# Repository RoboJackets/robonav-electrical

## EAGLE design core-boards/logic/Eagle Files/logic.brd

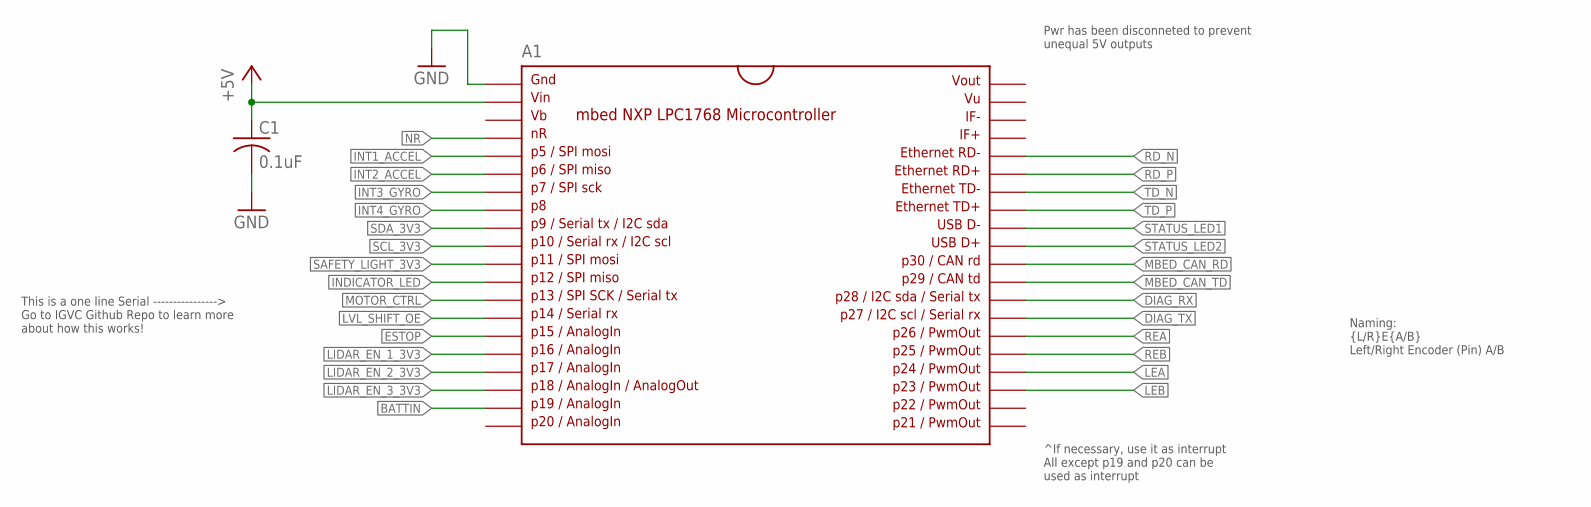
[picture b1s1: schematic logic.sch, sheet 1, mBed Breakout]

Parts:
A1: MBED1768; SPARKFUN-BOARDS_DIL40_0.9
C1: 0.1uF; C0603

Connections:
+5V: A1.2, C1.1; also elsewhere on the board
BATTIN: A1.19; also elsewhere on the board
DIAG_RX: A1.28; also elsewhere on the board
DIAG_TX: A1.27; also elsewhere on the board
ESTOP: A1.15; also elsewhere on the board
GND: A1.1, C1.2; also elsewhere on the board
INDICATOR_LED: A1.12; also elsewhere on the board
INT1_ACCEL: A1.5
INT2_ACCEL: A1.6
INT3_GYRO: A1.7
INT4_GYRO: A1.8
LEA: A1.24; also elsewhere on the board
LEB: A1.23; also elsewhere on the board
LIDAR_EN_1_3V3: A1.16; also elsewhere on the board
LIDAR_EN_2_3V3: A1.17; also elsewhere on the board
LIDAR_EN_3_3V3: A1.18; also elsewhere on the board
LVL_SHIFT_OE: A1.14; also elsewhere on the board
MBED_CAN_RD: A1.30; also elsewhere on the board
MBED_CAN_TD: A1.29; also elsewhere on the board
MOTOR_CTRL: A1.13; also elsewhere on the board
NR: A1.4; also elsewhere on the board
RD_N: A1.36; also elsewhere on the board
RD_P: A1.35; also elsewhere on the board
REA: A1.26; also elsewhere on the board
REB: A1.25; also elsewhere on the board
SAFETY_LIGHT_3V3: A1.11; also elsewhere on the board
SCL_3V3: A1.10; also elsewhere on the board
SDA_3V3: A1.9; also elsewhere on the board
STATUS_LED1: A1.32; also elsewhere on the board
STATUS_LED2: A1.31; also elsewhere on the board
TD_N: A1.34; also elsewhere on the board
TD_P: A1.33; also elsewhere on the board

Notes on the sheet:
Naming: {L/R}E{A/B} Left/Right Encoder (Pin) A/B
This is a one line Serial ----------------> Go to IGVC Github Repo to learn more about how this works!
^If necessary, use it as interrupt All except p19 and p20 can be used as interrupt
Pwr has been disconneted to prevent unequal 5V outputs

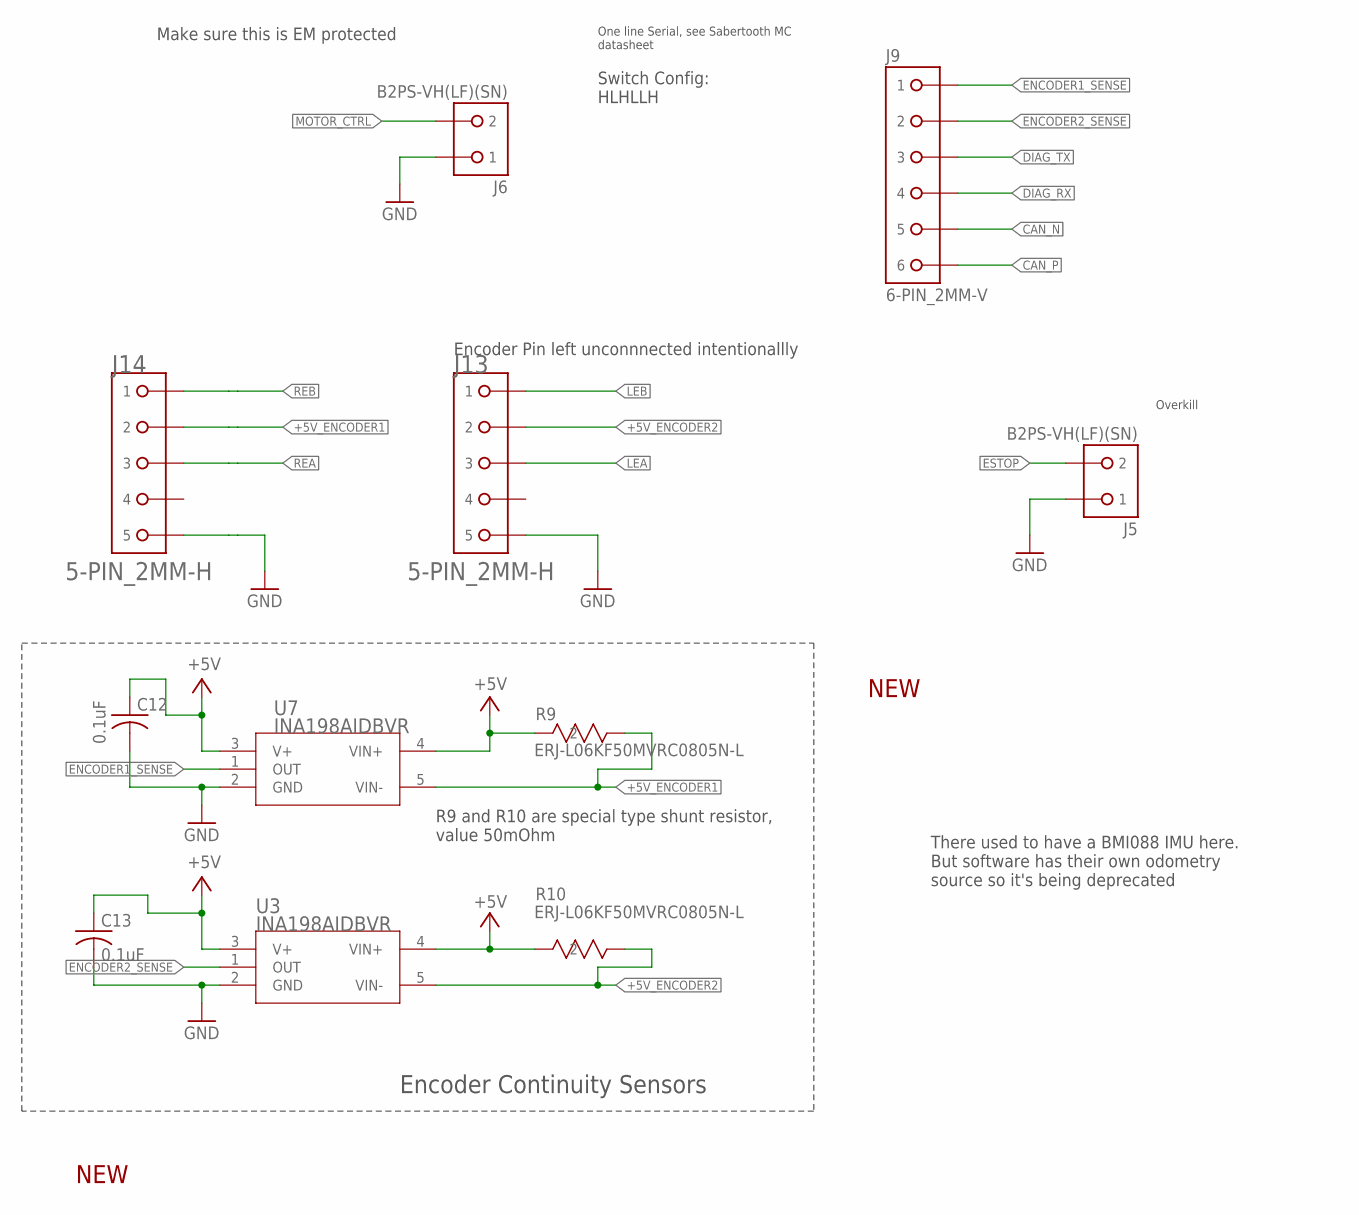
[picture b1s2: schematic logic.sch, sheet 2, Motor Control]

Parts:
C12, C13: 0.1uF; C0603
J5, J6: B2PS-VH(LF)(SN); B2PS-CENTERED
J9: 6-PIN_2MM-V; 2MM-6-V
J13, J14: 5-PIN_2MM-H; 2MM-5-H
R9, R10: ERJ-L06KF50MVRC0805N-L; RC0805N-L
U3, U7: INA198AIDBVR; DBV5

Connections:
+5V: C12.1, C13.1, R9.2, R10.2, U3.3 (V+), U3.4 (VIN+), U7.3 (V+), U7.4 (VIN+); also elsewhere on the board
+5V_ENCODER1: J14.2, R9.1, U7.5 (VIN-)
+5V_ENCODER2: J13.2, R10.1, U3.5 (VIN-)
CAN_N: J9.5; also elsewhere on the board
CAN_P: J9.6; also elsewhere on the board
DIAG_RX: J9.4; also elsewhere on the board
DIAG_TX: J9.3; also elsewhere on the board
ENCODER1_SENSE: J9.1, U7.1 (OUT)
ENCODER2_SENSE: J9.2, U3.1 (OUT)
ESTOP: J5.2; also elsewhere on the board
GND: C12.2, C13.2, J5.1, J6.1, J13.5, J14.5, U3.2 (GND), U7.2 (GND); also elsewhere on the board
LEA: J13.3; also elsewhere on the board
LEB: J13.1; also elsewhere on the board
MOTOR_CTRL: J6.2; also elsewhere on the board
REA: J14.3; also elsewhere on the board
REB: J14.1; also elsewhere on the board

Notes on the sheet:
Encoder Continuity Sensors
One line Serial, see Sabertooth MC datasheet
Encoder Pin left unconnnected intentionallly
Overkill
Make sure this is EM protected
There used to have a BMI088 IMU here. But software has their own odometry source so it's being deprecated
NEW
Switch Config: HLHLLH
R9 and R10 are special type shunt resistor, value 50mOhm

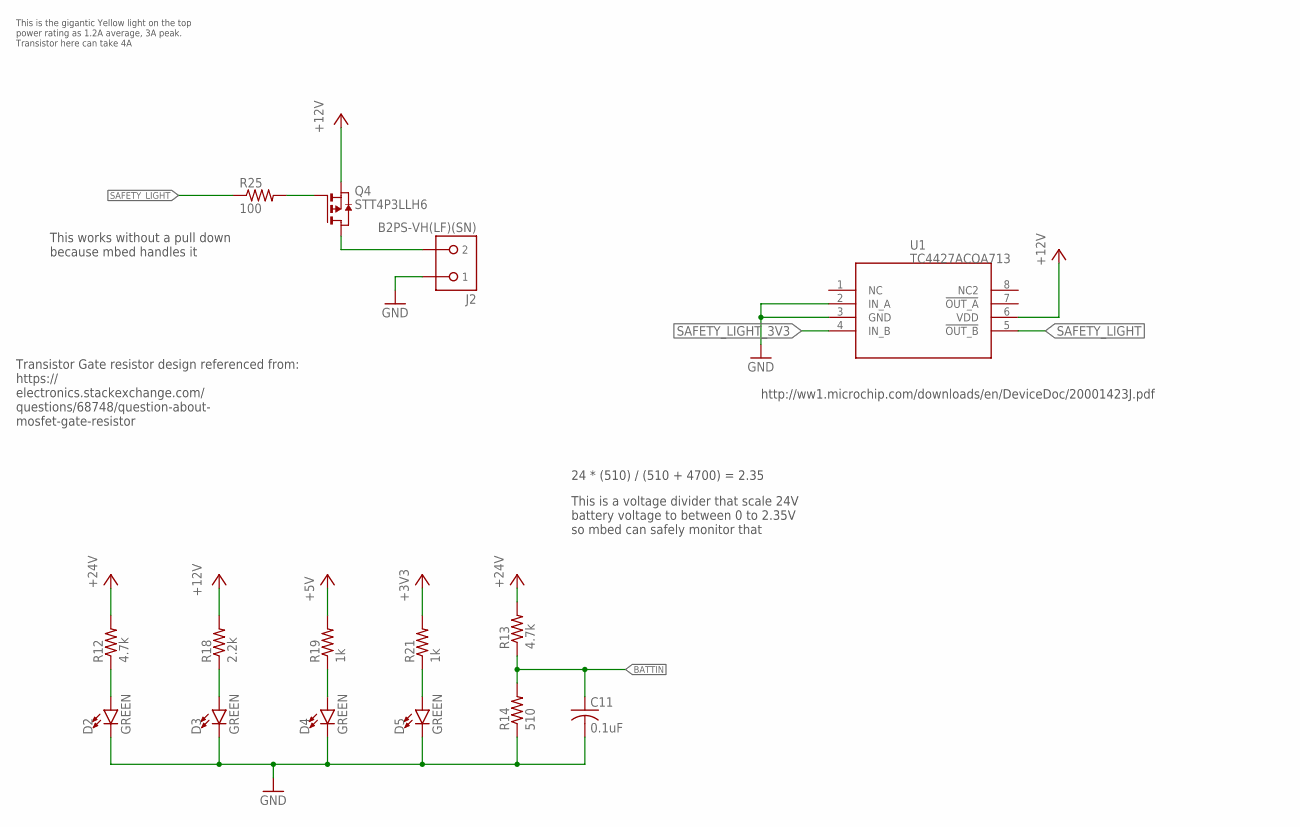
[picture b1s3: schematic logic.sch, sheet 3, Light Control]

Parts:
C11: 0.1uF; C0603
D2, D3, D4, D5: GREEN; LED-0603
J2: B2PS-VH(LF)(SN); B2PS-CENTERED
Q4: STT4P3LLH6; SOT23-6
R12, R13: 4.7k; R0603
R14: 510; R0603
R18: 2.2k; R0603
R19, R21: 1k; R0603
R25: 100; R0603
U1: TC4427ACOA713; SOIC-8

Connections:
3V3_LED_R: D5.A, R21.1
5V_LED_R: D4.A, R19.1
12V_LED_R: D3.A, R18.1
+3V3: R21.2; also elsewhere on the board
+5V: R19.2; also elsewhere on the board
+12V: Q4.4 (S), R18.2, U1.6 (VDD); also elsewhere on the board
+24V: R12.2, R13.2; also elsewhere on the board
BATTIN: C11.1, R13.1, R14.2; also elsewhere on the board
GND: C11.2, D2.C, D3.C, D4.C, D5.C, J2.1, R14.1, U1.2 (IN_A), U1.3 (GND); also elsewhere on the board
unnamed: D2.A, R12.1
SAFETY_HRD: J2.2, Q4.1 (D), Q4.2 (D), Q4.5 (D), Q4.6 (D)
SAFETY_LIGHT: R25.1, U1.5 (!OUT_B)
SAFETY_LIGHT_3V3: U1.4 (IN_B); also elsewhere on the board
SAFETY_R: Q4.3 (G), R25.2

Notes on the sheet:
This is the gigantic Yellow light on the top power rating as 1.2A average, 3A peak. Transistor here can take 4A
24 * (510) / (510 + 4700) = 2.35
Transistor Gate resistor design referenced from: https:// electronics.stackexchange.com/ questions/68748/question-about- mosfet-gate-resistor
http://ww1.microchip.com/downloads/en/DeviceDoc/20001423J.pdf
This is a voltage divider that scale 24V battery voltage to between 0 to 2.35V so mbed can safely monitor that
This works without a pull down because mbed handles it

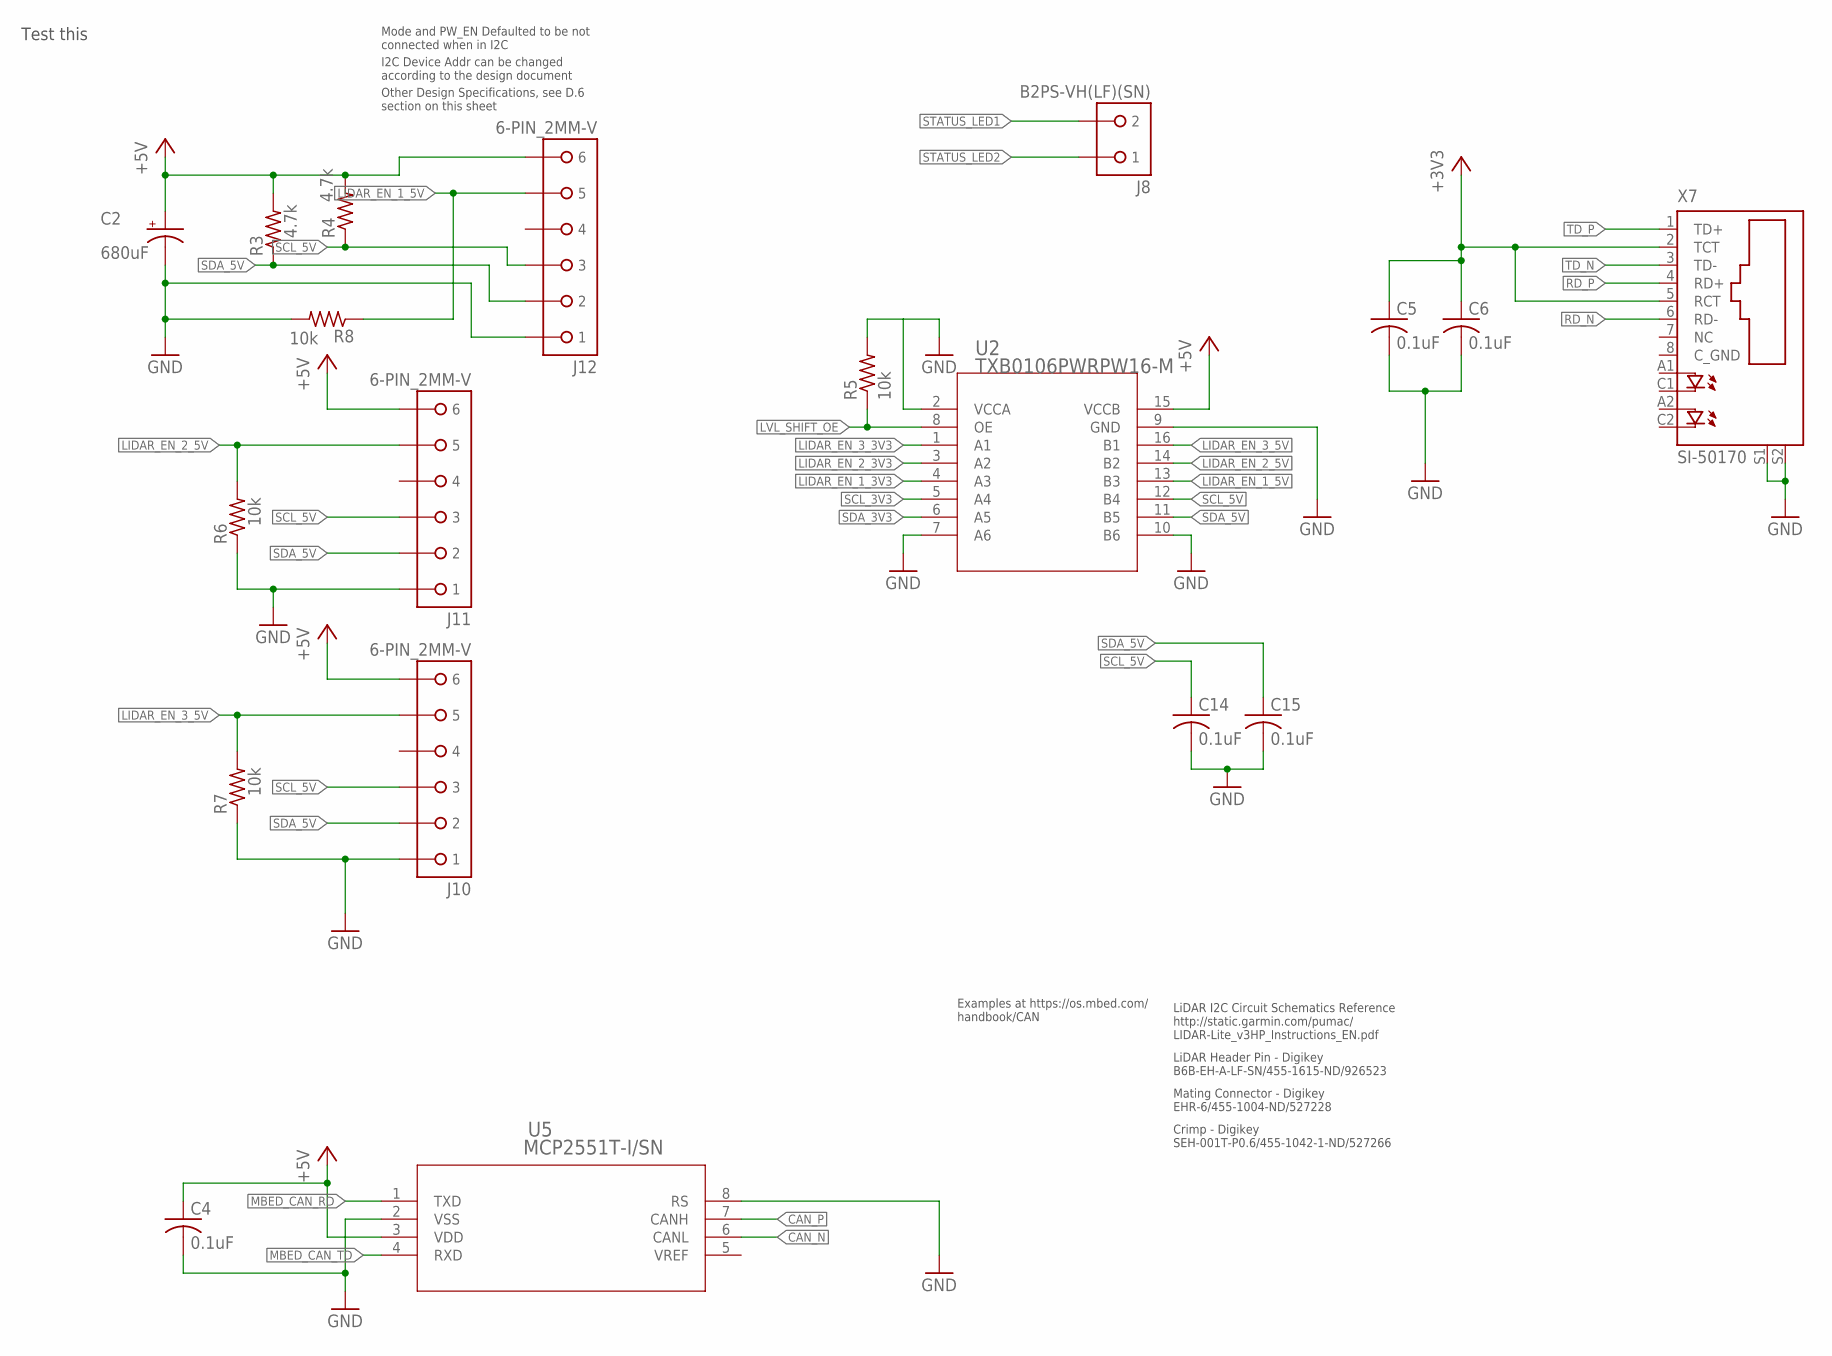
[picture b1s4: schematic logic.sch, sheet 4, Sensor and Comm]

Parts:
C2: 680uF; E5-5
C4, C5, C6, C14, C15: 0.1uF; C0603
J8: B2PS-VH(LF)(SN); B2PS-CENTERED
J10, J11, J12: 6-PIN_2MM-V; 2MM-6-V
R3, R4: 4.7k; R0603
R5, R6, R7, R8: 10k; R0603
U2: TXB0106PWRPW16-M; PW16-M
U5: MCP2551T-I/SN; SOIC8-N_MC
X7: SI-50170

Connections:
+3V3: C5.1, C6.1, X7.2 (TCT), X7.5 (RCT); also elsewhere on the board
+5V: C2.+, C4.1, J10.6, J11.6, J12.6, R3.2, R4.2, U2.15 (VCCB), U5.3 (VDD); also elsewhere on the board
CAN_N: U5.6 (CANL); also elsewhere on the board
CAN_P: U5.7 (CANH); also elsewhere on the board
GND: C2.-, C4.2, C5.2, C6.2, C14.2, C15.2, J10.1, J11.1, J12.1, R5.2, R6.1, R7.1, R8.2, U2.2 (VCCA), U2.7 (A6), U2.9 (GND), U2.10 (B6), U5.2 (VSS), U5.8 (RS), X7.S1, X7.S2; also elsewhere on the board
LIDAR_EN_1_3V3: U2.4 (A3); also elsewhere on the board
LIDAR_EN_1_5V: J12.5, R8.1, U2.13 (B3)
LIDAR_EN_2_3V3: U2.3 (A2); also elsewhere on the board
LIDAR_EN_2_5V: J11.5, R6.2, U2.14 (B2)
LIDAR_EN_3_3V3: U2.1 (A1); also elsewhere on the board
LIDAR_EN_3_5V: J10.5, R7.2, U2.16 (B1)
LVL_SHIFT_OE: R5.1, U2.8 (OE); also elsewhere on the board
MBED_CAN_RD: U5.1 (TXD); also elsewhere on the board
MBED_CAN_TD: U5.4 (RXD); also elsewhere on the board
RD_N: X7.6 (RD-); also elsewhere on the board
RD_P: X7.4 (RD+); also elsewhere on the board
SCL_3V3: U2.5 (A4); also elsewhere on the board
SCL_5V: C14.1, J10.3, J11.3, J12.3, R4.1, U2.12 (B4)
SDA_3V3: U2.6 (A5); also elsewhere on the board
SDA_5V: C15.1, J10.2, J11.2, J12.2, R3.1, U2.11 (B5)
STATUS_LED1: J8.2; also elsewhere on the board
STATUS_LED2: J8.1; also elsewhere on the board
TD_N: X7.3 (TD-); also elsewhere on the board
TD_P: X7.1 (TD+); also elsewhere on the board

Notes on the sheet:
LiDAR I2C Circuit Schematics Reference http://static.garmin.com/pumac/ LIDAR-Lite_v3HP_Instructions_EN.pdf
I2C Device Addr can be changed according to the design document
LiDAR Header Pin - Digikey B6B-EH-A-LF-SN/455-1615-ND/926523
Mating Connector - Digikey EHR-6/455-1004-ND/527228
Crimp - Digikey SEH-001T-P0.6/455-1042-1-ND/527266
Mode and PW_EN Defaulted to be not connected when in I2C
Examples at https://os.mbed.com/ handbook/CAN
Other Design Specifications, see D.6 section on this sheet
Test this

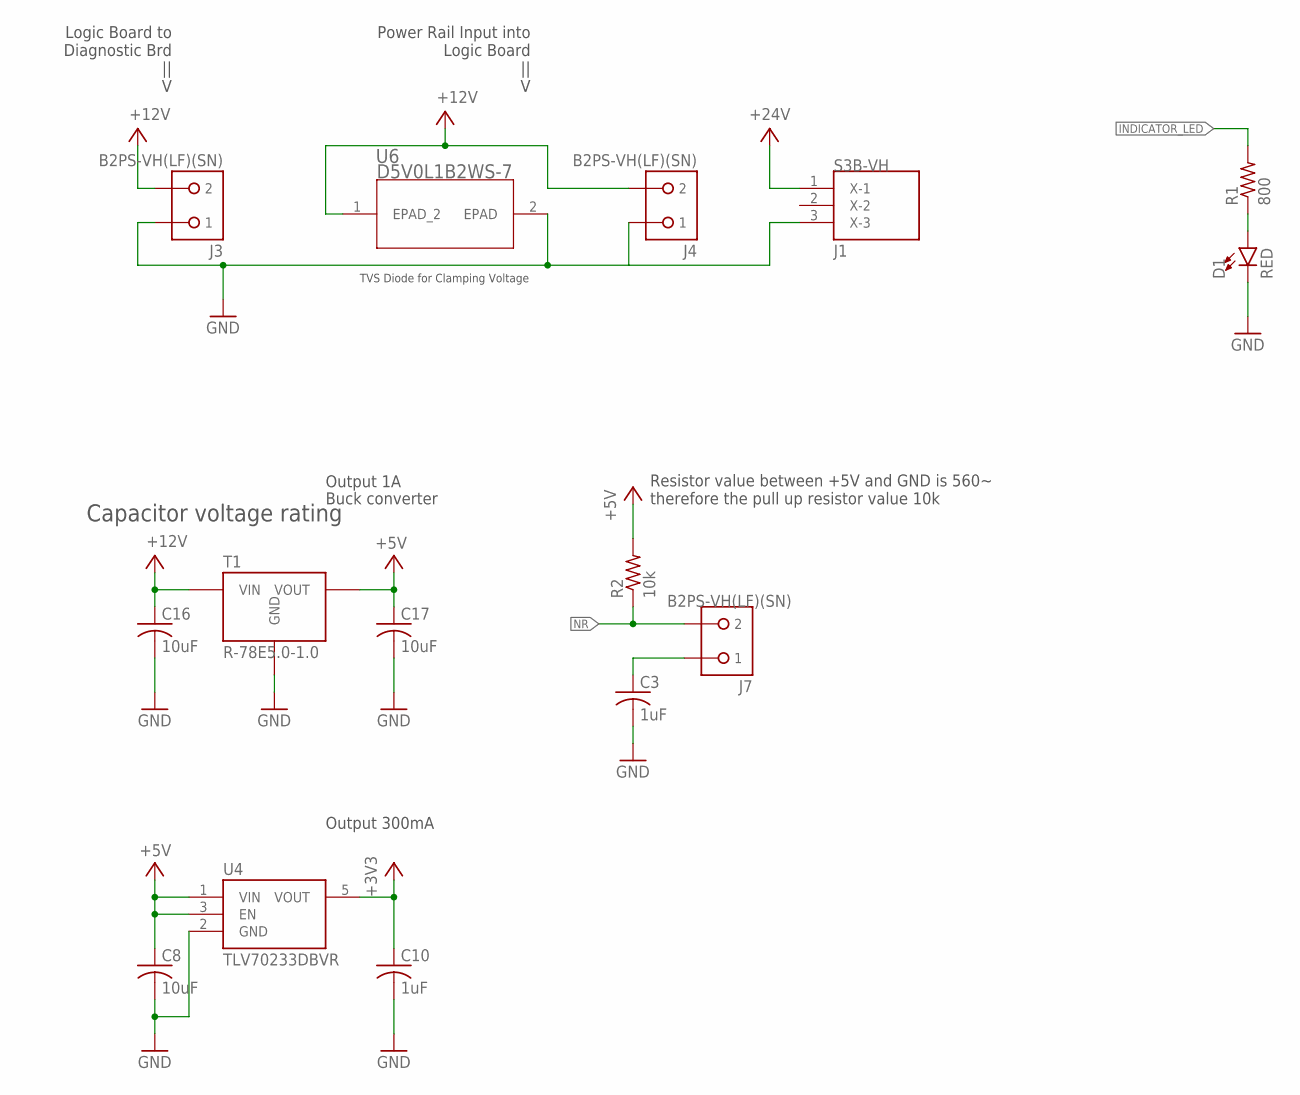
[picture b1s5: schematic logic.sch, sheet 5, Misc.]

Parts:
C3, C10: 1uF; C0805
C8, C16, C17: 10uF; C0805
D1: RED; LED-0603
J1: S3B-VH
J3, J4, J7: B2PS-VH(LF)(SN); B2PS-CENTERED
R1: 800; R0603
R2: 10k; R0603
T1: R-78E5.0-1.0; R-78E
U4: TLV70233DBVR; SOT-23-5
U6: D5V0L1B2WS-7; SOD323

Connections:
+3V3: C10.1, U4.5 (VOUT); also elsewhere on the board
+5V: C8.1, C17.1, R2.2, T1.3 (VOUT), U4.1 (VIN), U4.3 (EN); also elsewhere on the board
+12V: C16.1, J3.2, J4.2, T1.1 (VIN), U6.1 (EPAD_2); also elsewhere on the board
+24V: J1.1 (X-1); also elsewhere on the board
GND: C3.2, C8.2, C10.2, C16.2, C17.2, D1.C, J1.3 (X-3), J3.1, J4.1, T1.2 (GND), U4.2 (GND), U6.2 (EPAD); also elsewhere on the board
INDICATOR_LED: R1.2; also elsewhere on the board
unnamed: D1.A, R1.1
unnamed: C3.1, J7.1
NR: J7.2, R2.1; also elsewhere on the board

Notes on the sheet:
Buck converter
Output 1A
Output 300mA
Power Rail Input into Logic Board || V
Logic Board to Diagnostic Brd || V
Capacitor voltage rating
Resistor value between +5V and GND is 560~ therefore the pull up resistor value 10k
TVS Diode for Clamping Voltage

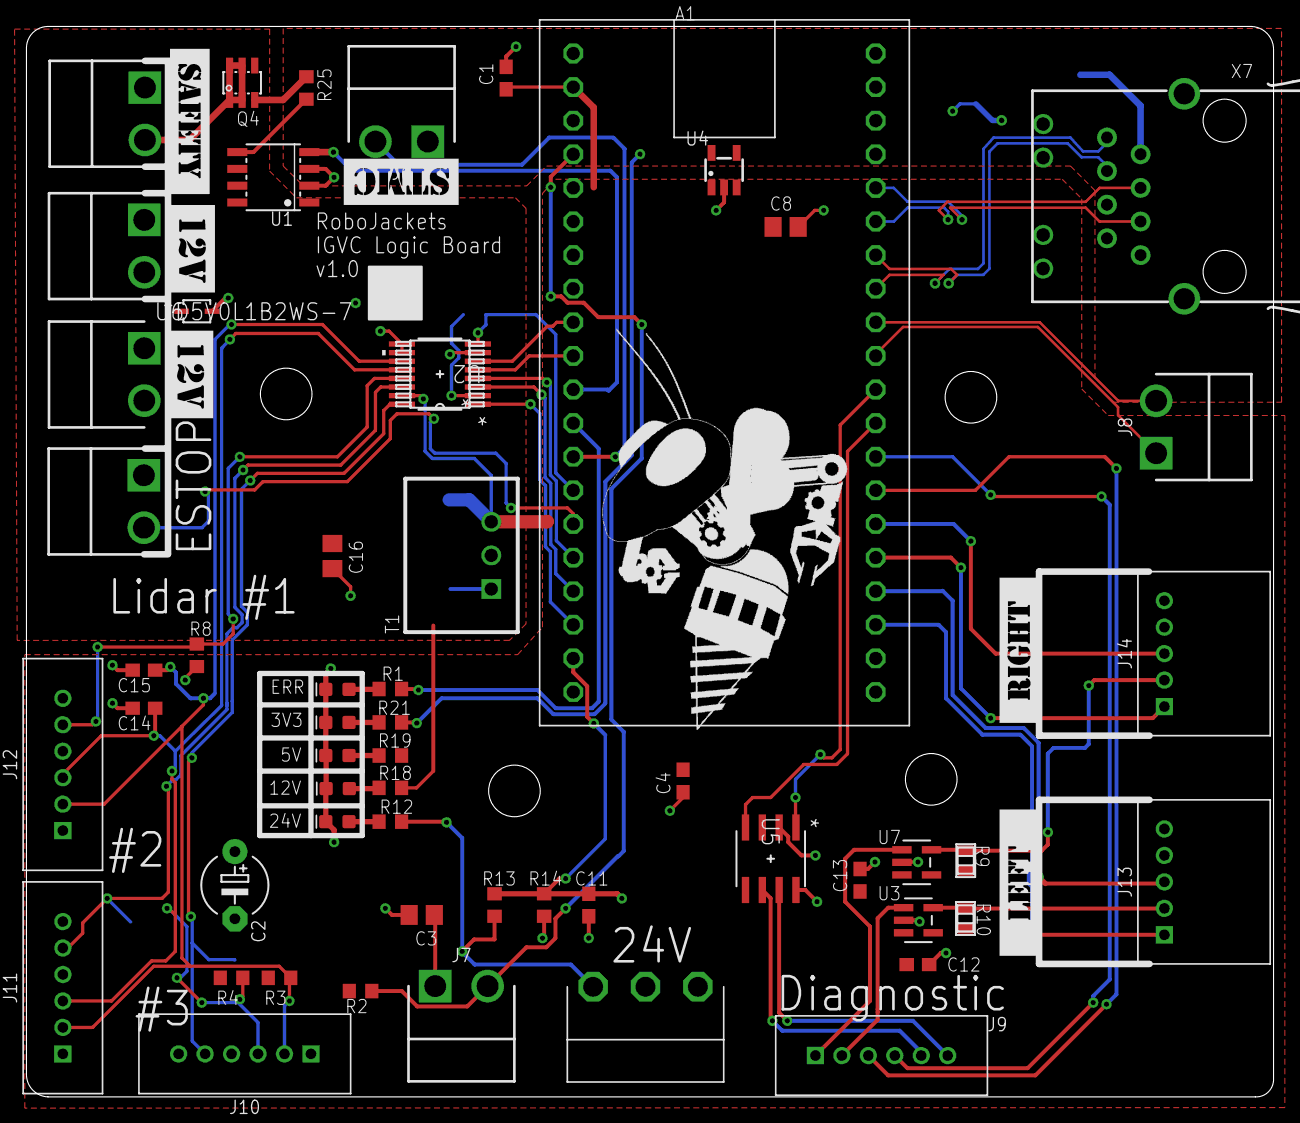
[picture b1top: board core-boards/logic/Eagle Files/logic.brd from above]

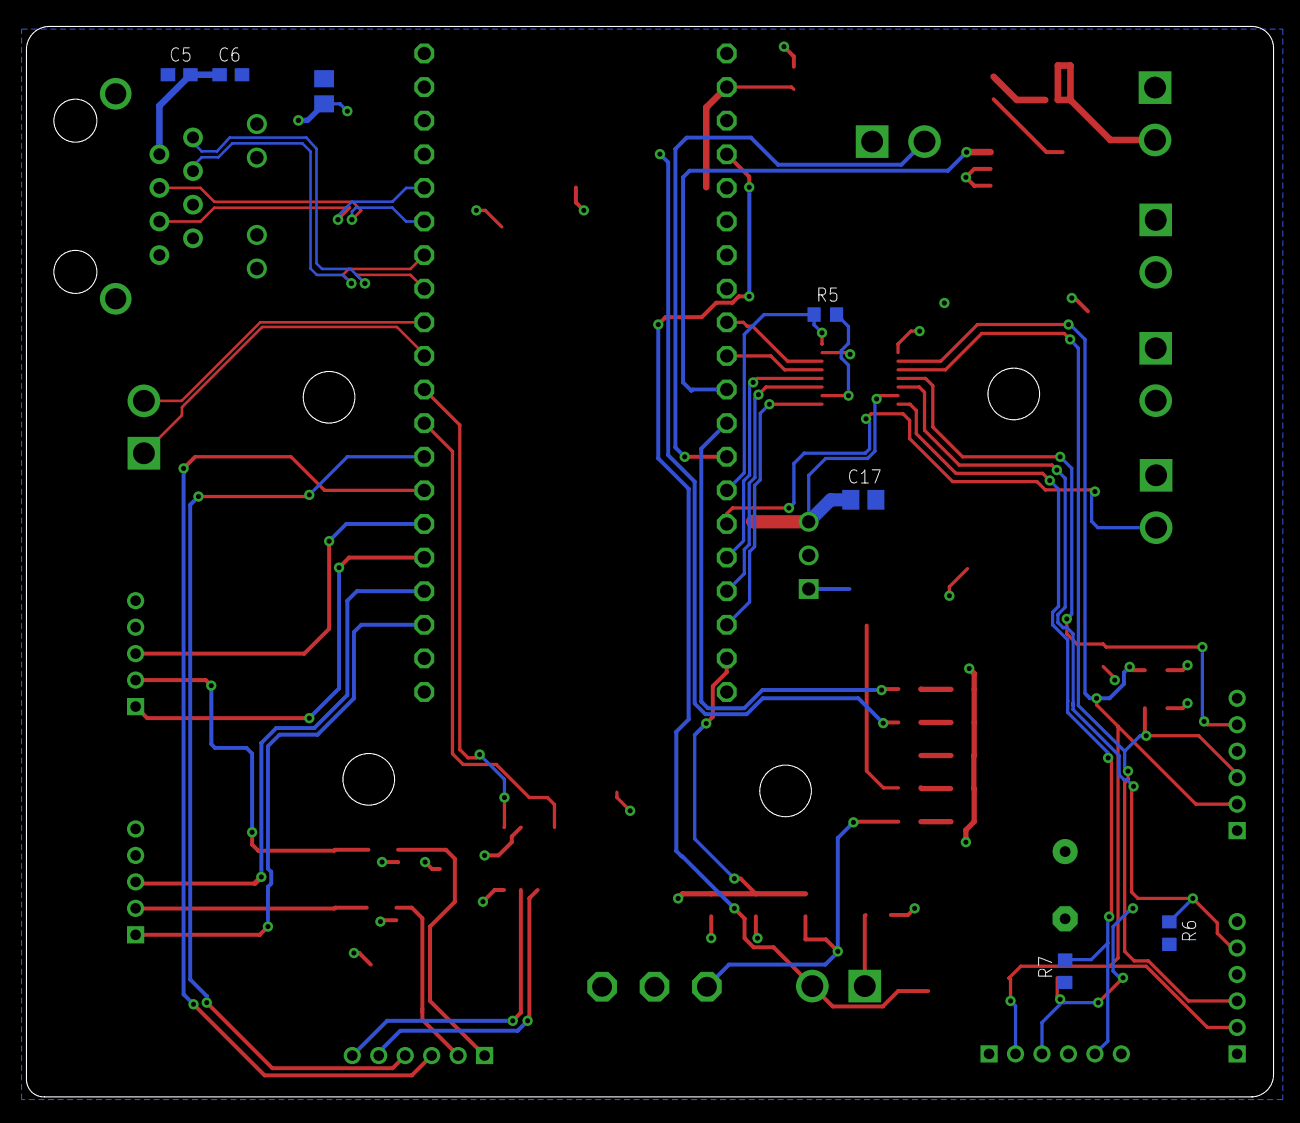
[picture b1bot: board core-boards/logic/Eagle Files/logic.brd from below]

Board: 2 copper layers, 94.2 x 80.9 mm, 73 parts (7 on the bottom side), 51 nets.

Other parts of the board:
U$1, U$2, U$3, U$4: STANDOFF-HOLE
U$5, U$7: 12V
U$10: ROBOBUZZ_1.4X
U$12: SAFETY
U$13: LEFT
U$14: RIGHT
U$16: STMC

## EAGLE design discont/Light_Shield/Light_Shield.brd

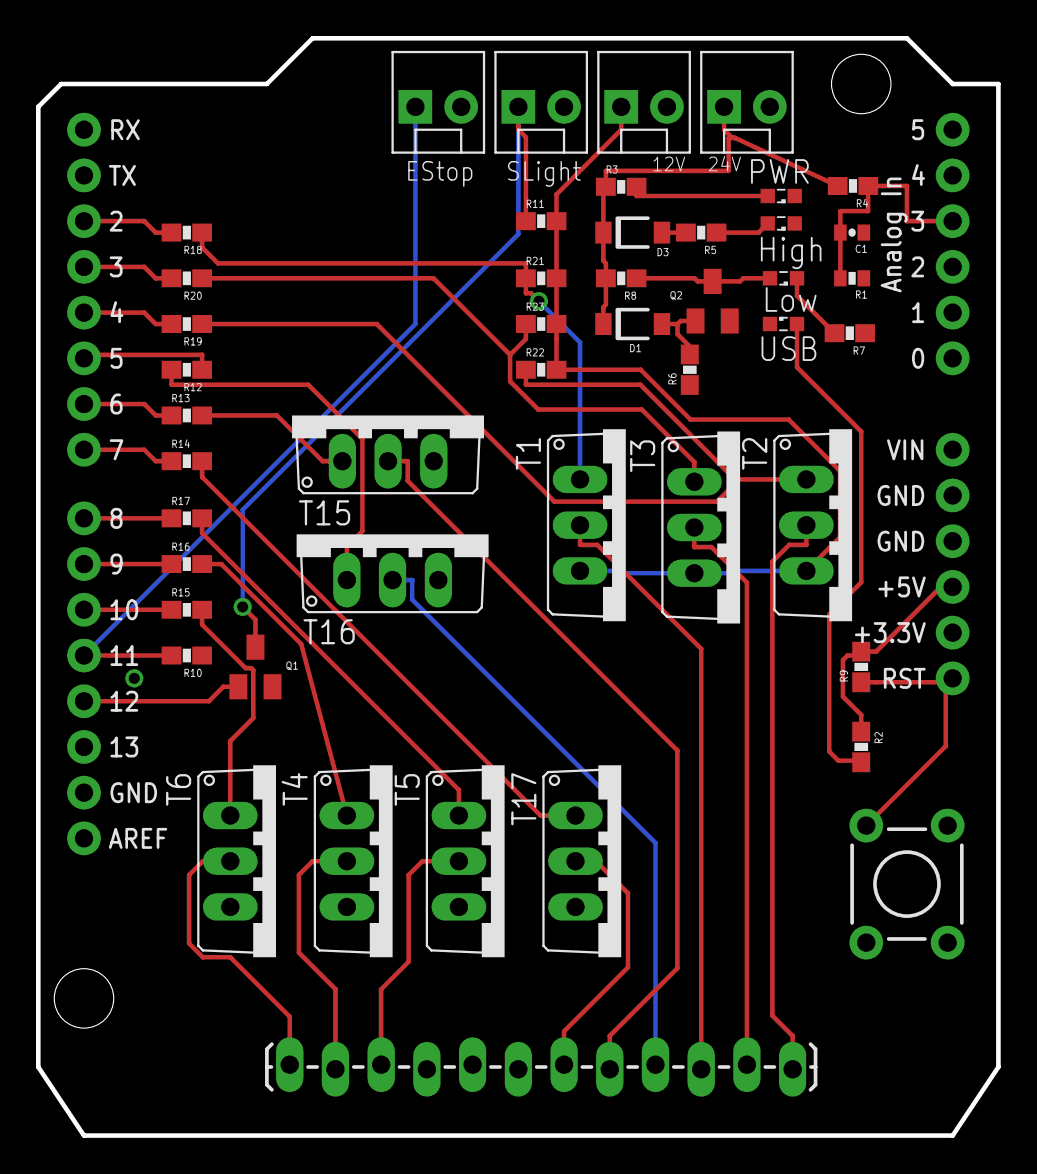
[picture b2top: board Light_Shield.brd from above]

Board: 2 copper layers, 53.3 x 61.0 mm, 49 parts (0 on the bottom side), 43 nets.

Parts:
C1: 0.1uF; 0402-CAP
D1: DIODE-ZENER-BT; SOD123FL
D3: BA340A; SOD123FL
FRAME1: FRAME-LEDGER; CREATIVE_COMMONS
JP1, JP2, JP3, JP4: M02POLAR; MOLEX-1X2
JP5: Underglow; 1X12_LOCK_LONGPADS
LED1: High; SML0603
LED2: Low; SML0603
LED3: PWR; SML0603
LED4: USB; SML0603
Q1, Q2: BC846ASMD; SOT23
R1: 536; 0402-RES
R2, R3, R4, R5, R8, R9, R10, R11, R18, R19, R20: 2700; 0603-RES
R6, R7, R12, R13, R14, R15, R16, R17, R21, R22, R23: 200; 0603-RES
S1: RESET; TACTILE-PTH
T1, T2, T3, T4, T5, T6, T15, T16, T17: TO220V
U1: ARDUINO_SHIELDLABEL; DUEMILANOVE_SHIELD

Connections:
1S1_CTRL: R12.1, U1.D5
1S1_OUT: JP5.4, T16.2
1S2_CTRL: R13.1, U1.D6
1S2_OUT: JP5.5, T15.2
1S3_CTRL: R14.1, U1.D7
1S3_OUT: JP5.6, T17.2
2S1_CTRL: R17.1, U1.D8
2S1_OUT: JP5.10, T5.2
2S2_CTRL: R16.1, U1.D9
2S2_OUT: JP5.11, T4.2
2S3_CTRL: R15.1, U1.D10
2S3_OUT: JP5.12, T6.2
5V: R2.1, R9.2, U1.5V
12V: JP4.1, R11.2, R21.2, R22.2, R23.2, T1.3, T2.3, T3.3
24V: D1.C, D3.C, JP3.1, R3.1, R4.2, R8.2
BLUE_CTRL: R19.2, U1.D4
BLUE_OUT: JP5.1, T2.2
GND: C1.1, JP3.2, JP4.2, LED1.C, LED3.C, LED4.C, Q1.2, Q2.2, R1.1, R6.1, R7.1, R10.1, S1.1, T4.3, T5.3, T6.3, T15.3, T16.3, T17.3, U1.GND@0
GREEN_CTRL: R20.2, U1.D3
GREEN_OUT: JP5.2, T3.2
unnamed: C1.2, R1.2, R4.1, U1.A3
unnamed: LED3.A, R3.2
unnamed: LED2.A, Q2.3, R8.1
unnamed: D1.A, Q2.1, R6.2
unnamed: LED4.A, R2.2
unnamed: JP2.1, Q1.3, R11.1
unnamed: D3.A, R5.2
unnamed: LED1.A, R5.1
unnamed: R18.1, R21.1, T1.1
unnamed: LED2.C, R7.2
unnamed: R17.2, T5.1
unnamed: R9.1, S1.3, U1.RES
unnamed: R16.2, T4.1
unnamed: R15.2, T6.1
unnamed: R14.2, T17.1
unnamed: R13.2, T15.1
unnamed: R12.2, T16.1
unnamed: R19.1, R22.1, T2.1
unnamed: R20.1, R23.1, T3.1
RED_CTRL: R18.2, U1.D2
RED_OUT: JP5.3, T1.2
SAFETY_LIGHT: Q1.1, U1.D12
SW_OFF: JP1.1, R10.2, U1.D11

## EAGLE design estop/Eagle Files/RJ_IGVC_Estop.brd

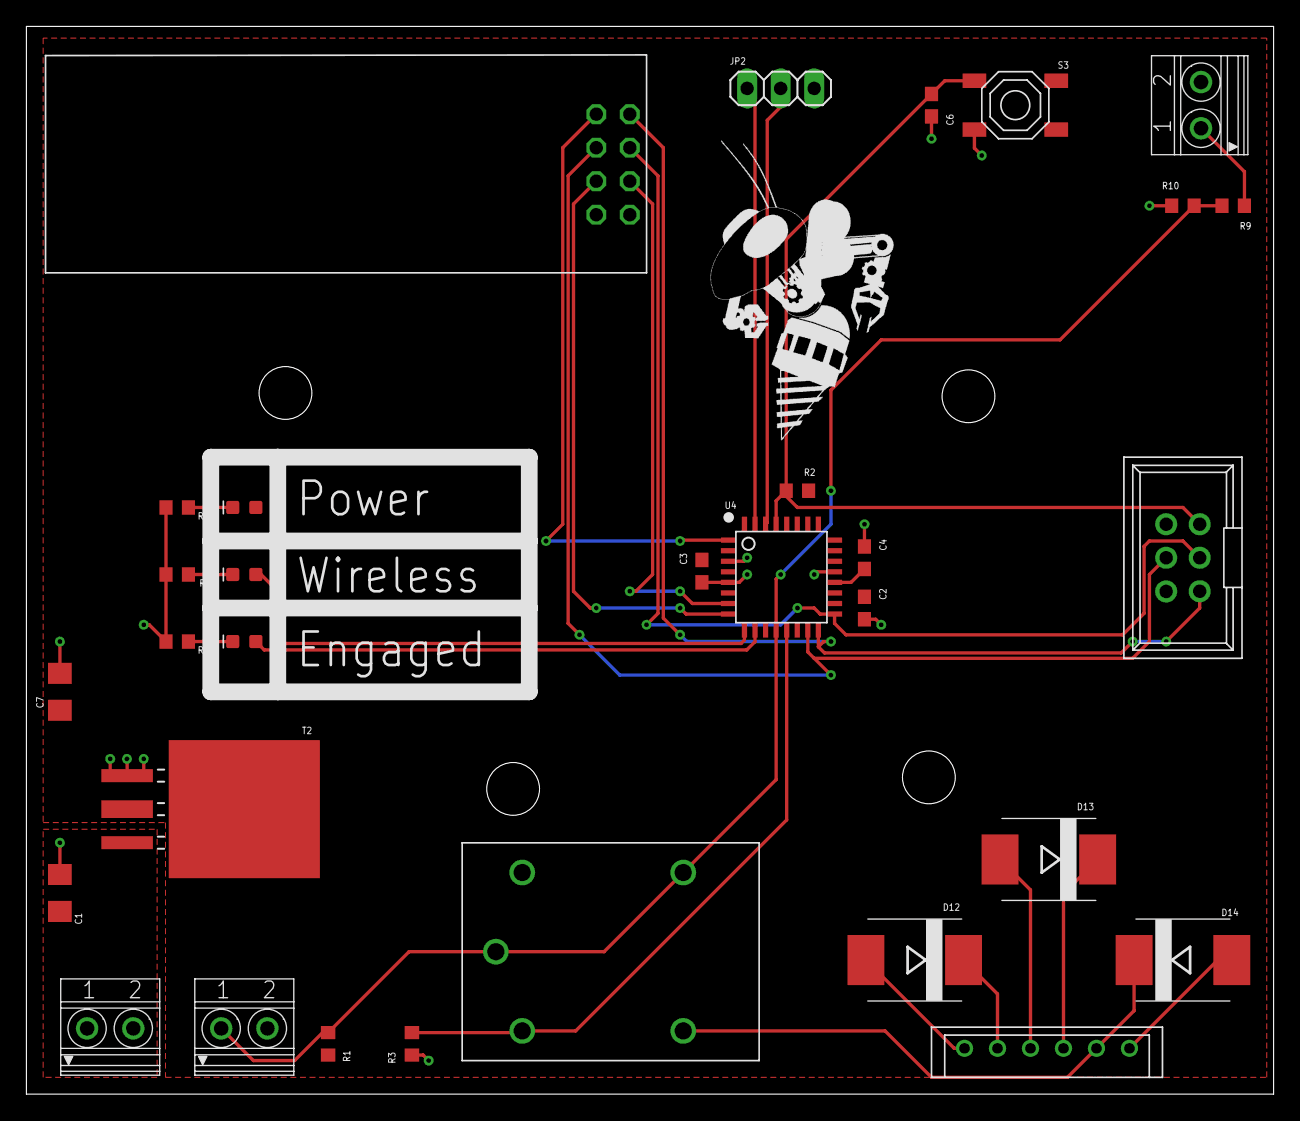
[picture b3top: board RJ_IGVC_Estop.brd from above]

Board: 2 copper layers, 94.5 x 80.9 mm, 32 parts (0 on the bottom side), 26 nets.

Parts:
C1, C7: 10uF; C1206
C2, C3, C4, C6: 0.1uF; C0603
D1, D2, D3: Green; LED-0603
D12, D13, D14: S10M-TP; SMC
JP2: Serial; 1X03
PROG: ICSP Connector; 2X3SHROUDED
R1, R2, R3: 10k; R0603
R4, R5, R6: 1k; R0603
R9: 4.7k; R0603
R10: 750; R0603
S3: SKQGADE010; SW4-SMD-5.2X5.2X1.5MM
T2: LD1086D2M33TR; D2PAK/A
U4: ATMEGA328P-AUR
U$1: G5LE-14
U$2: ROBOBUZZ_1.2X
X2: Power; 1751248
X3: Button In; 1751248
X4: E-Stop Signal In; 1751248
X5: NRF24L01+PA+LNA
X6: B6B-EH-A(LF)(SN); B6BEHALFSN

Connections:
!RESET: C6.1, PROG.!RESET, R2.1, S3.1, U4.29
+3V3: C2.1, C3.1, C7.1, D2.A, PROG.+5V, R1.1, R2.2, T2.2, U4.4, U4.6, U4.18, X5.VCC
+24V: D12.A, X6.X-1
BUTTON_LED: D1.A, U4.9
CE: U4.7, X5.CE
CSN: U4.8, X5.CSN
DIODE_TO_GREEN: D12.C, X6.X-2
DIODE_TO_INTER: D13.C, X6.X-4
GND: C1.2, C2.2, C3.2, C4.2, C6.2, C7.2, D14.A, JP2.3, PROG.GND, R3.1, R4.1, R5.1, R6.1, R10.2, S3.4, T2.1, U4.3, U4.5, U4.21, U$1.P$1, X2.2, X3.2, X4.2, X5.GND, X6.X-6
IN: R1.2, R9.2, R10.1, U4.12, U$1.P$2, U$1.P$4, X3.1
IRQ: U4.1, X5.IRQ
MISO: PROG.MISO, U4.16, X5.MISO
MOSI: PROG.MOSI, U4.15, X5.MOSI
MOTOR_POWER: D13.A, X6.X-3
unnamed: D2.C, R5.2
unnamed: D1.C, R4.2
unnamed: D3.C, R6.2
unnamed: R9.1, X4.1
unnamed: C4.1, U4.20
OUT: R3.2, U4.13, U$1.P$3
RX: JP2.2, U4.30
SCK: PROG.SCK, U4.17, X5.SCK
SOLENOID_TRIG: D14.C, U$1.P$5, X6.X-5
TX: JP2.1, U4.31
V_IN: C1.1, T2.3, X2.1
WIRELESS_LED: D3.A, U4.10

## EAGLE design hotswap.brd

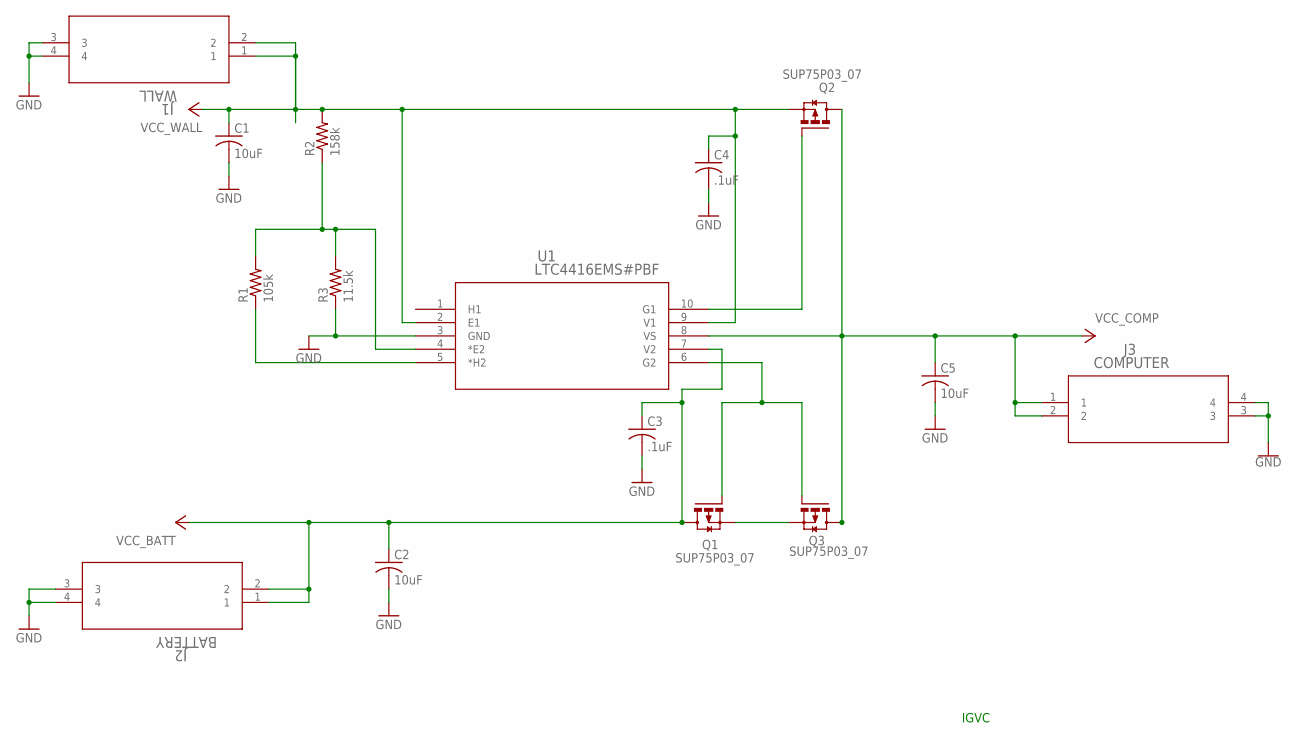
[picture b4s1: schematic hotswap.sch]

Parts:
C1, C2, C5: 10uF; C1210
C3, C4: .1uF; C0805
J1: WALL; 641737-1
J2: BATTERY; 641737-1
J3: COMPUTER; 641737-1
Q1, Q2, Q3: SUP75P03_07; DPACK_2
R1: 105k; R0603
R2: 158k; R0603
R3: 11.5k; R0603
U1: LTC4416EMS#PBF; MSOP-10_MS

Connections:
GND: C1.2, C2.2, C3.2, C4.2, C5.2, J1.3, J1.4, J2.3, J2.4, J3.3, J3.4, R3.1, U1.3 (GND)
unnamed: Q1.S, Q3.S
unnamed: Q1.G, Q3.G, U1.6 (G2)
unnamed: Q2.G, U1.10 (G1)
unnamed: R1.2, R2.1, R3.2, U1.4 (*E2)
unnamed: R1.1, U1.5 (*H2)
VCC_BATT: C2.1, C3.1, J2.1, J2.2, Q1.D, U1.7 (V2)
VCC_COMP: C5.1, J3.1, J3.2, Q2.D, Q3.D, U1.8 (VS)
VCC_WALL: C1.1, C4.1, J1.1, J1.2, Q2.S, R2.2, U1.2 (E1), U1.9 (V1)

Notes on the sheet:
IGVC

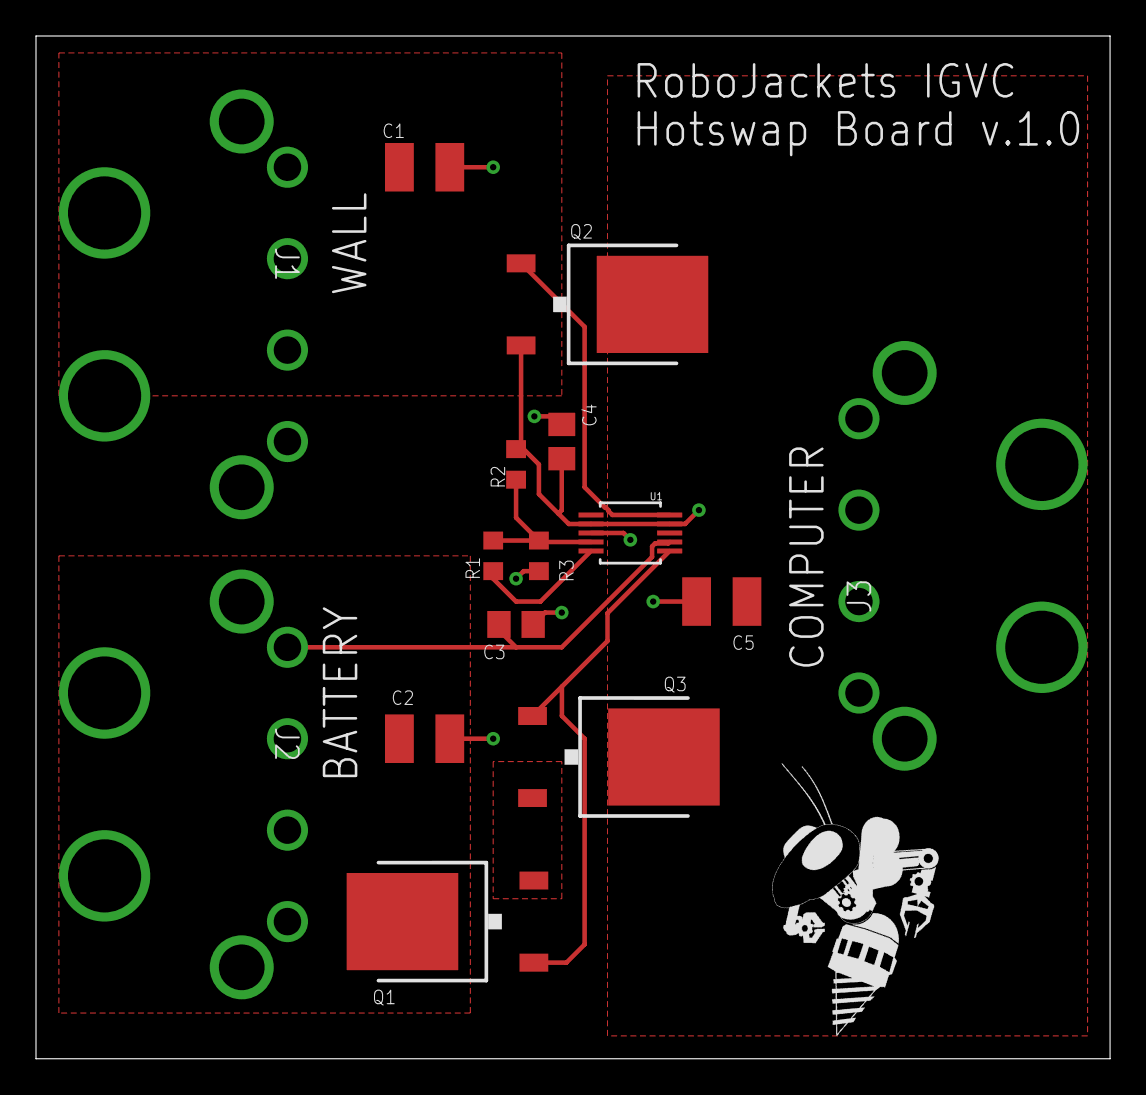
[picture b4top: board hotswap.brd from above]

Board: 2 copper layers, 59.7 x 56.8 mm, 16 parts (0 on the bottom side), 9 nets.

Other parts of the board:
E$1: ROBOBUZZ_0.8X

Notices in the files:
parts and their libraries:
SparkFun-LED: Licensing: Creative Commons ShareAlike 4.0 International - https://creativecommons.org/licenses/by-sa/4.0
SparkFun-Boards: Licensing: CC v3.0 Share-Alike You are welcome to use this library for commercial purposes.
SparkFun-Aesthetics: http://creativecommons.org/licenses/by-sa/3.0
